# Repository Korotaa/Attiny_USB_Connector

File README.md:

# Attiny_USB_Connector

Designed with Kicad :

- 2 layers
- Attiny 8 bits MCU
- USB connector

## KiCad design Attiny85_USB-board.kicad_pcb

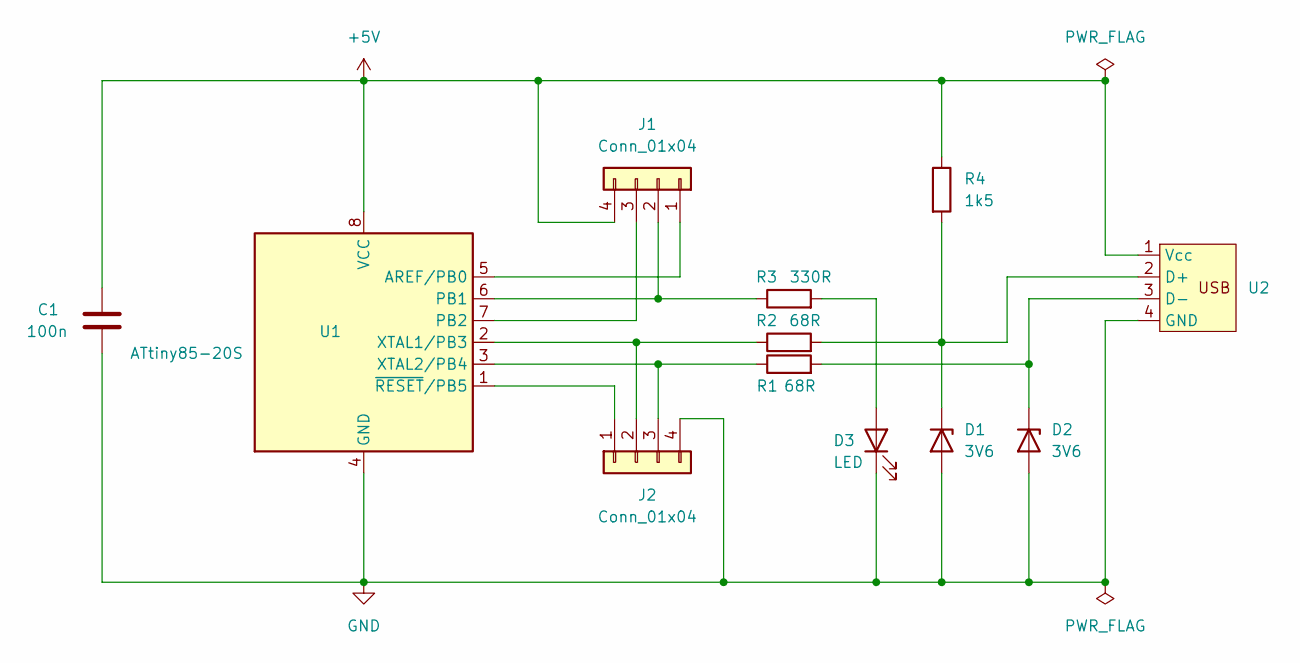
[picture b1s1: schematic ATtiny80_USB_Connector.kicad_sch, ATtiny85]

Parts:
C1: 100n; C_1206_3216Metric_Pad1.33x1.80mm_HandSolder
D1, D2: 3V6; D_SOD-123
D3: LED; LED_D3.0mm
J1, J2: Conn_01x04; PinHeader_1x04_P1.00mm_Vertical
R1, R2: 68R; R_0201_0603Metric
R3: 330R; R_0201_0603Metric
R4: 1k5; R_0201_0603Metric
U1: ATtiny85-20S; SOIC-8-1EP_3.9x4.9mm_P1.27mm_EP2.29x3mm
U2: USB_connector

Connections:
+5V: C1.1, J1.4, R4.1, U1.8 (VCC), U2.1 (Vcc)
GND: C1.2, D1.2 (A), D2.2 (A), D3.1 (K), J2.4, U1.4 (GND), U2.4 (GND)
unnamed: D1.1 (K), R2.2, R4.2, U2.2 (D+)
unnamed: D2.1 (K), R1.2, U2.3 (D-)
unnamed: D3.2 (A), R3.2
unnamed: J1.1, U1.5 (AREF/PB0)
unnamed: J1.2, R3.1, U1.6 (PB1)
unnamed: J1.3, U1.7 (PB2)
unnamed: J2.1, U1.1 (~RESET/PB5)
unnamed: J2.2, R2.1, U1.2 (XTAL1/PB3)
unnamed: J2.3, R1.1, U1.3 (XTAL2/PB4)

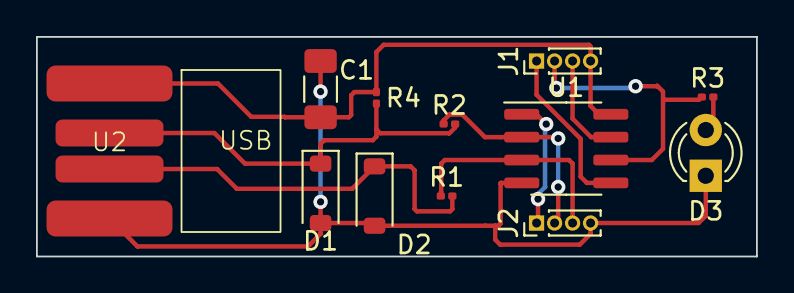
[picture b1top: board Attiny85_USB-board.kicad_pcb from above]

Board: 2 copper layers, 40.0 x 12.2 mm, 12 parts (0 on the bottom side), 11 nets.
